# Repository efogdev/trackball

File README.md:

## Endgame Trackball (hardware)

#### Why 6 layers?

Because it's cheaper than 4 layers. Yes, seriously.

#### Stackup

JLC06161H-3313

#### Also see

Parent repo: https://github.com/efogtech/endgame-trackball

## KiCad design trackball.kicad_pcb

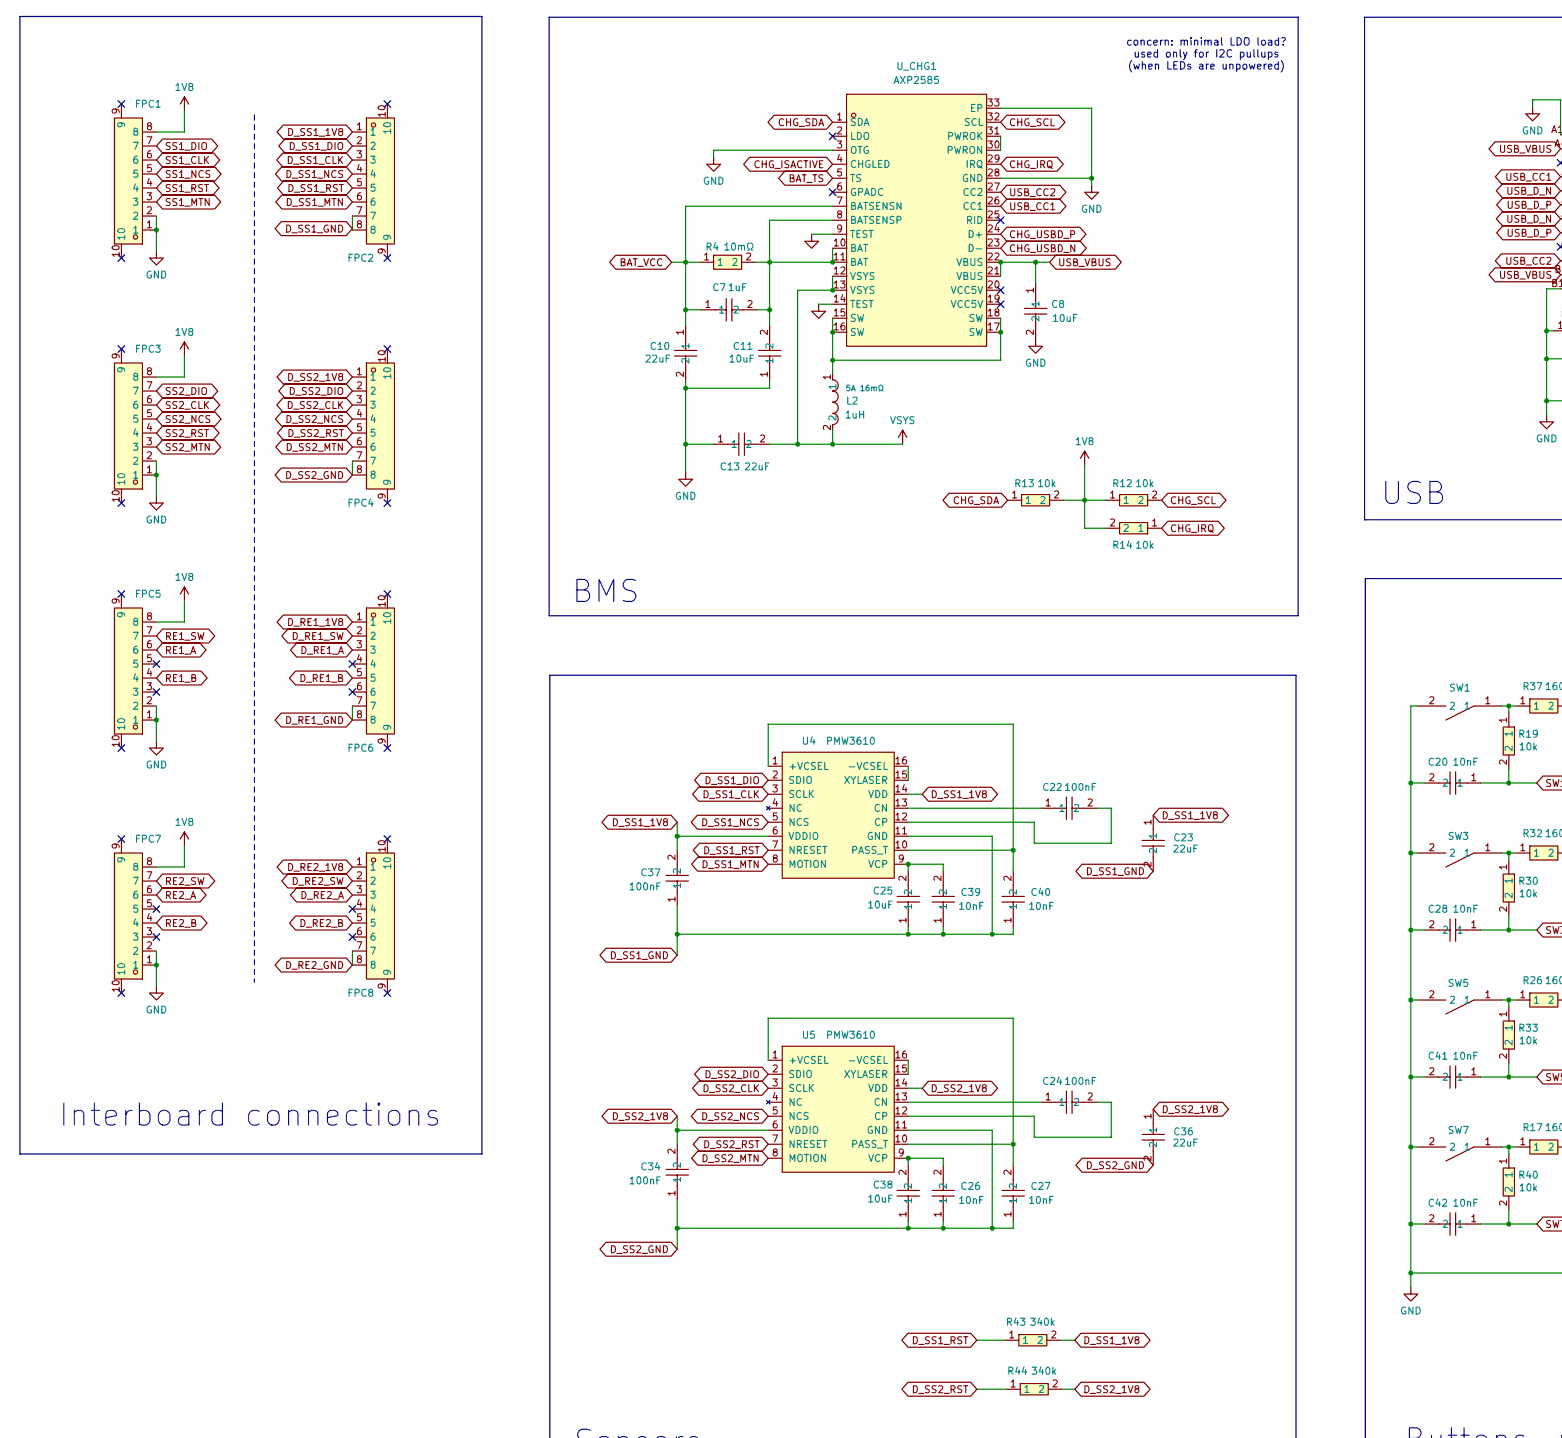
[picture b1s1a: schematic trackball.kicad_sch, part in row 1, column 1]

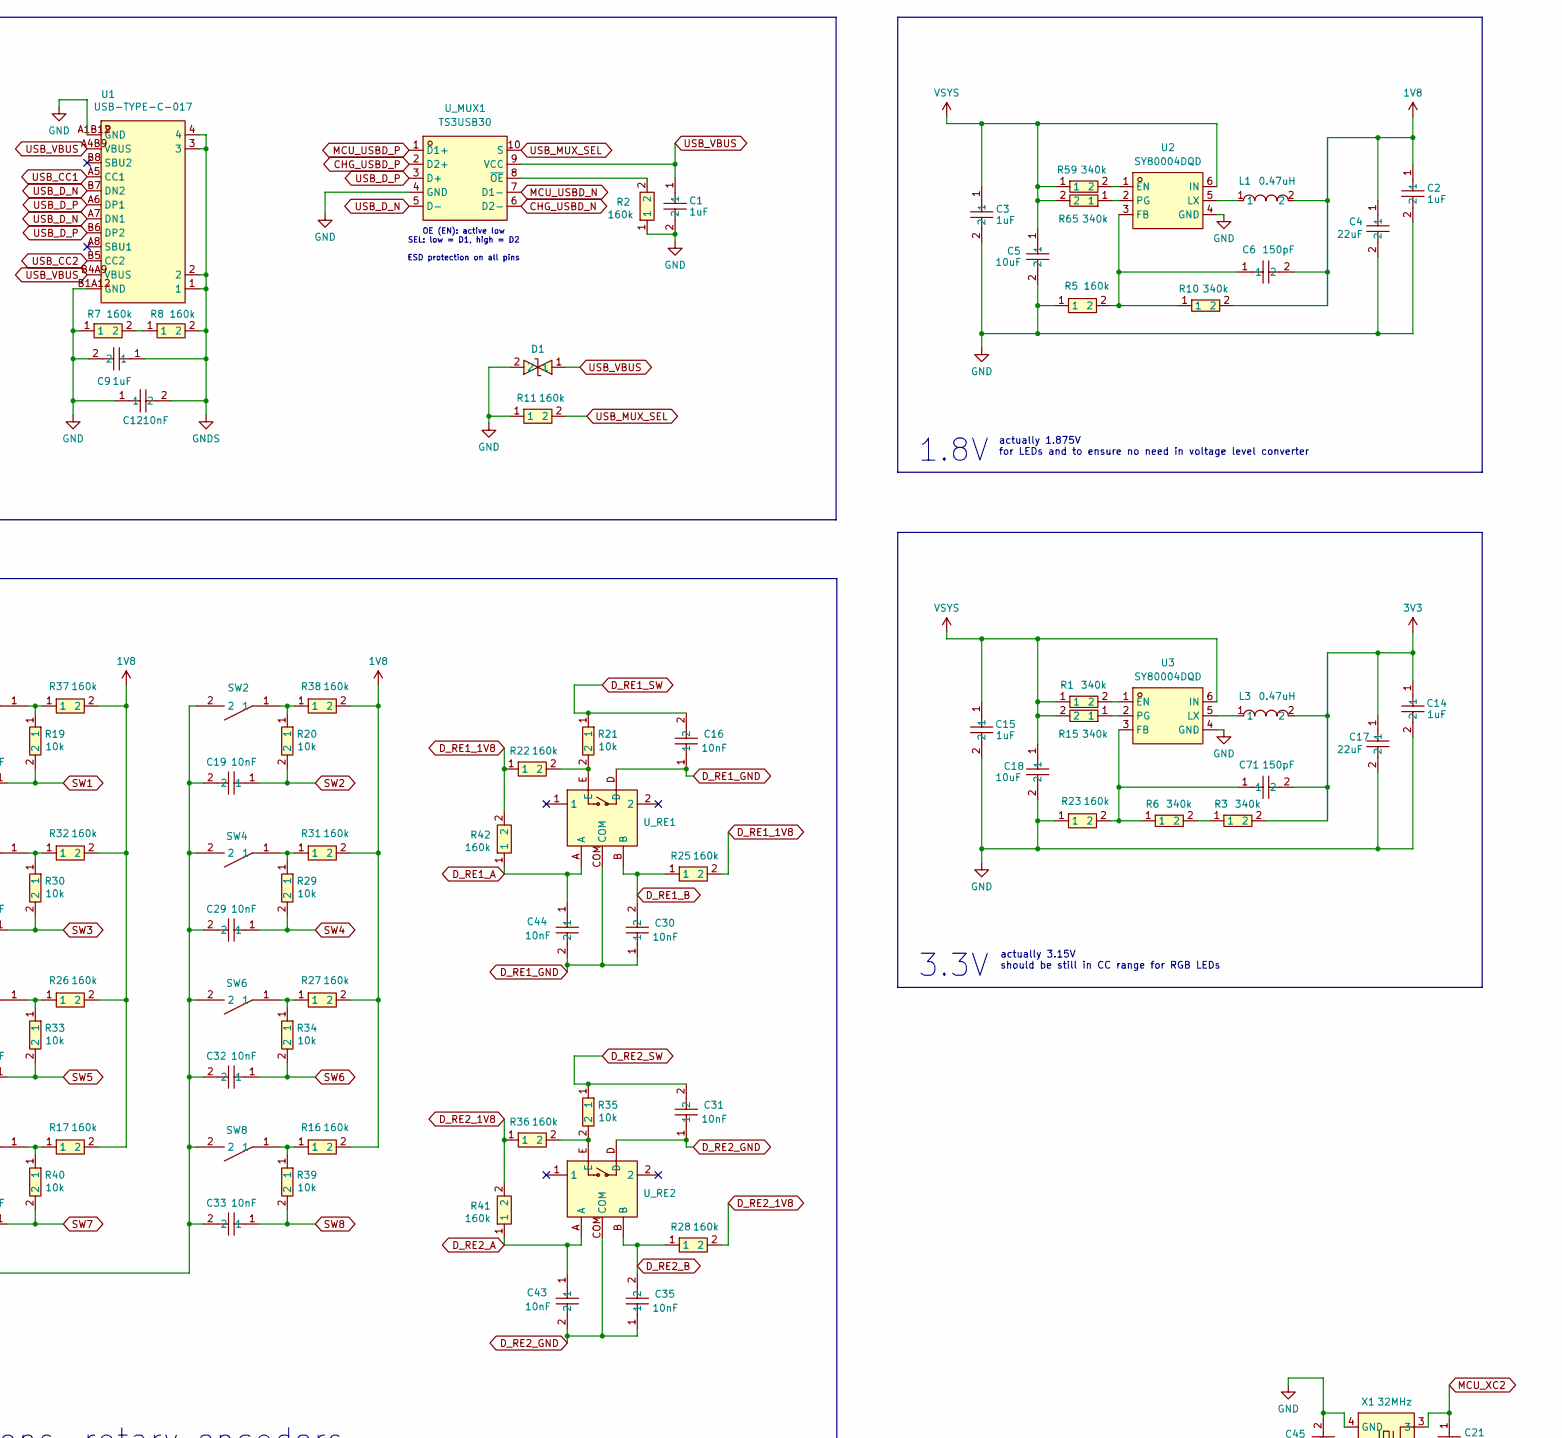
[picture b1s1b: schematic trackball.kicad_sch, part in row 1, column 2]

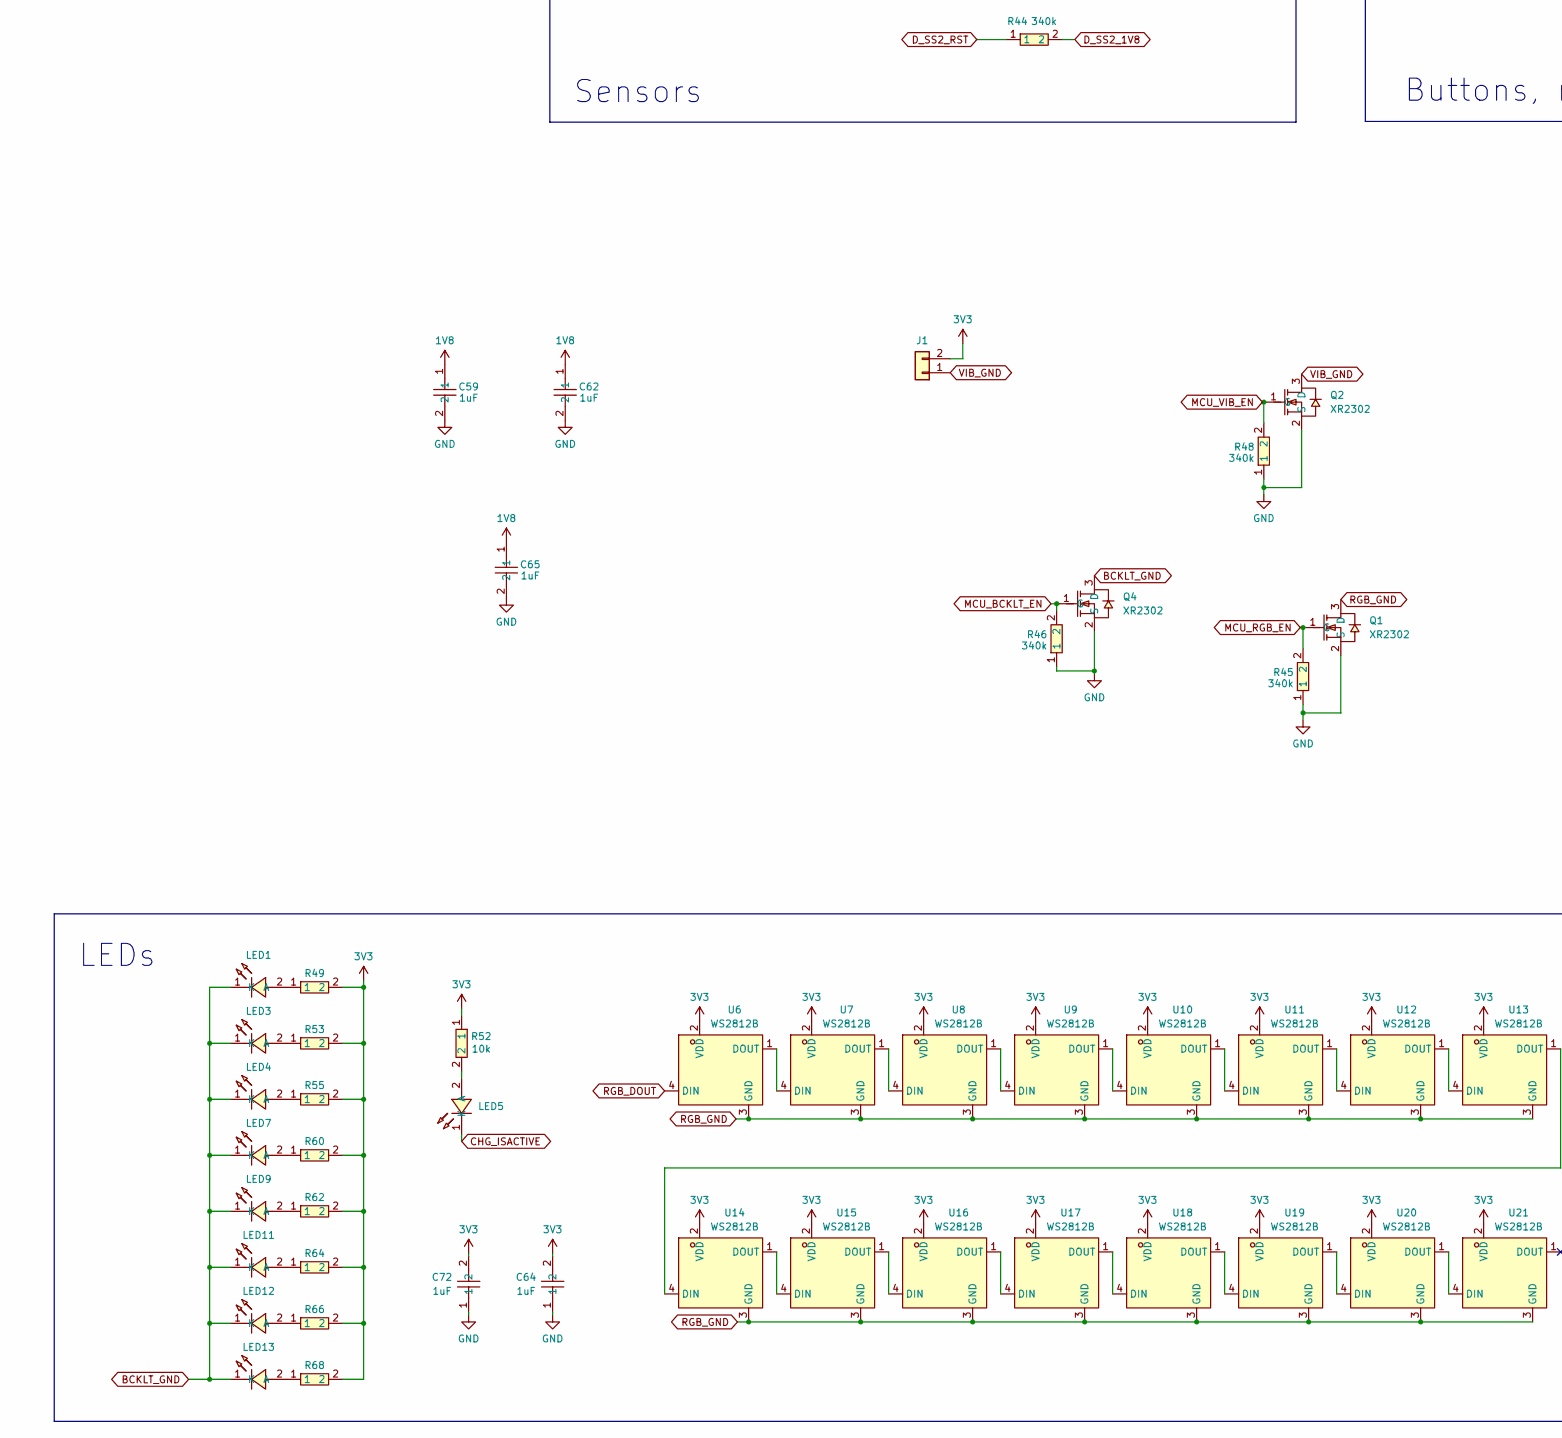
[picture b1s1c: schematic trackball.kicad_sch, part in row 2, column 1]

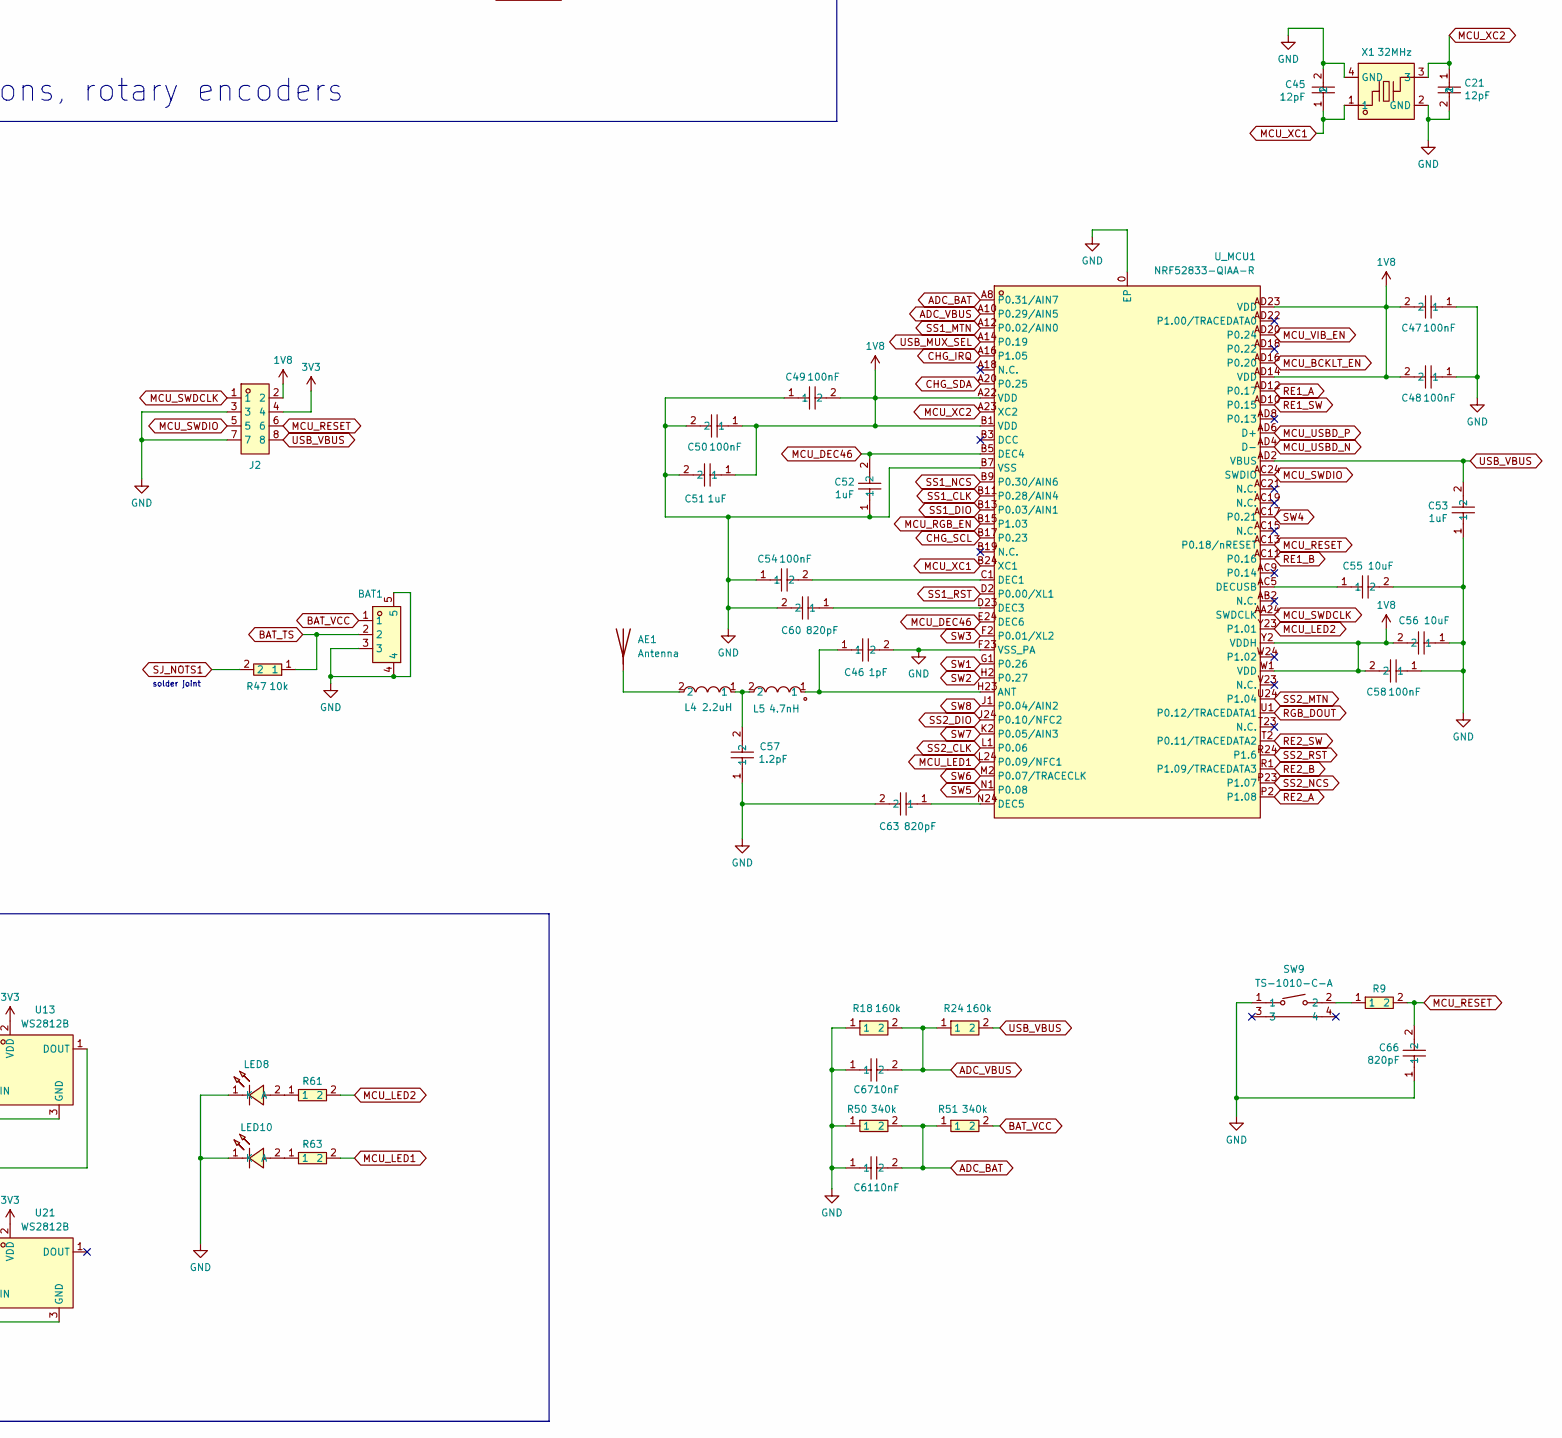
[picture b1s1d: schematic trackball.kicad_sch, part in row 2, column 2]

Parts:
AE1: Antenna; Texas_SWRA117D_2.4GHz_Left
BAT1: HCZZ0032-3; CONN-SMD_HCZZ0032-3; LCSC Part C7433424
C1, C2, C3, C7, C9, C14, C15, C51, C52, C53, C59, C62, C64, C65, C72: CGA0201X5R105M6R3ET; C0201; LCSC Part C6119749
C4, C10, C13, C17, C23, C36: GRM155R60J226ME11D; C0402; LCSC Part C415703
C5, C8, C11, C18, C25, C38, C55, C56: CL05A106MP5NUNC_C315248; C0402; LCSC Part C315248
C6, C71: C0201; LCSC Part C18213206
C12, C16, C19, C20, C26, C27, C28, C29, C30, C31, C32, C33, C35, C39, C40, C41, C42, C43, C44, C61, C67: 0201B103K160NT; C0201; LCSC Part C285154
C21, C45: 0201CG120J500NT; C0201; LCSC Part C50391
C22, C24, C34, C37, C47, C48, C49, C50, C54, C58: CGA0201X5R104K100ET; C0201; LCSC Part C6119757
C46: 0201CG1R0C250NT; C0201; LCSC Part C301901
C57: CGA0201C0G1R2C500ET; C0201; LCSC Part C22374839
C60, C63, C66: 0201B821K500NT; C0201; LCSC Part C2836759
D1: 0402ESDA-05N; D0402-BI; LCSC Part C316049
FPC1, FPC2, FPC3, FPC4, FPC5, FPC6, FPC7, FPC8: AFH34-S08FIA-1H; FPC-SMD_8P-P0.50_JS_AFH34-S08FIA-1H; LCSC Part C5139822
J1: Conn_01x02
J2: ZX-PM2.0-2-4PY; HDR-TH_8P-P2.00-V-F-R2-C4-S2.00; LCSC Part C7499368
L1, L3: FTC252012SR47MBCA; IND-SMD_L2.5-W2.0; LCSC Part C5832368
L2: FTC252012S1R0MBCD; L1008; LCSC Part C22400405
L4: LQG15HS2N2S02D; L0402; LCSC Part C86061
L5: LQG15HS4N7S02D; L0402-R-RD; LCSC Part C86065
LED1, LED3, LED4, LED7, LED9, LED11, LED12, LED13: SZYY0402W; LED0402-RD_WHITE; LCSC Part C434448
LED5: XL-1005UGC; LED0402-RD_GREEN; LCSC Part C965793
LED8, LED10: TZ-P2-0402RTIA1-0.45T; LED0402-RD_RED; LCSC Part C779449
Q1, Q2, Q4: XR2302; SOT-23-3_L2.9-W1.3-P0.95-LS2.4-BR; LCSC Part C42456447
R1, R3, R6, R10, R12, R13, R14, R15, R19, R20, R21, R29, R30, R33, R34, R35, R39, R40, R43, R44, R45, R46, R47, R48, R50, R51, R52, R59, R65: RC-01W103JT; R0201; LCSC Part C304504
R2, R5, R7, R8, R11, R16, R17, R18, R22, R23, R24, R25, R26, R27, R28, R31, R32, R36, R37, R38, R41, R42: 0201WMF1603TEE; R0201; LCSC Part C423714
R4: FRM121WFR010TM; R1206; LCSC Part C7467248
R9, R49, R53, R55, R60, R61, R62, R63, R64, R66, R68: RT0402BRE0750RL; R0402; LCSC Part C853312
SW1, SW2, SW3, SW4, SW5, SW6, SW7, SW8: HX TC-5608-Y; SW-SMD_TC-5608-Y; LCSC Part C25168853
SW9: TS-1010-C-A; KEY-SMD_TX-1010-X-X; LCSC Part C692458
U1: USB-TYPE-C-017; USB-TYPE-C-SMD_C9900008089; LCSC Part C2927037
U2, U3: SY80004DQD; VSON-6_L1.5-W1.5-P0.50-TL; LCSC Part C20617244
U4, U5: PMW3610
U6, U7, U8, U9, U10, U11, U12, U13, U14, U15, U16, U17, U18, U19, U20, U21: WS2812B; LED-SMD_4P-L1.0-W1.0-TL_XL-1010RGBC-WS2812B; LCSC Part C5349953
U_CHG1: AXP2585; QFN-32_L5.0-W5.0-P0.40-TL-EP2.9; LCSC Part C20199912
U_MCU1: NRF52833-QIAA-R; AQFN-73_L7.0-W7.0-P0.50-BL-EP4.8; LCSC Part C504799
U_MUX1: TS3USB30; UQFN-10_L1.8-W1.4-P0.40-TL; LCSC Part C73880
U_RE1, U_RE2: GT-EVA01AA-L1; RES-ADJ-SMD_GT-EVA01AA-L1; LCSC Part C17702124
X1: XL7EL89CKI-111YLC-32M; CRYSTAL-SMD_4P-L2.0-W1.6-BL; LCSC Part C2965582

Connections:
1V8: C2.1, C4.1, C6.2, C47.2, C48.2, C49.2, C50.1, C51.1, C56.2, C58.2, C59.1, C62.1, C65.1, FPC1.8, FPC3.8, FPC5.8, FPC7.8, J2.2, L1.2, R10.2, R12.1, R13.2, R14.2, R16.2, R17.2, R26.2, R27.2, R31.2, R32.2, R37.2, R38.2, U_MCU1.A22 (VDD), U_MCU1.AD14 (VDD), U_MCU1.AD23 (VDD), U_MCU1.B1 (VDD), U_MCU1.W1 (VDD), U_MCU1.Y2 (VDDH)
3V3: C14.1, C17.1, C64.2, C71.2, C72.2, J1.2, J2.4, L3.2, R3.2, R49.2, R52.1, R53.2, R55.2, R60.2, R62.2, R64.2, R66.2, R68.2, U6.2 (VDD), U7.2 (VDD), U8.2 (VDD), U9.2 (VDD), U10.2 (VDD), U11.2 (VDD), U12.2 (VDD), U13.2 (VDD), U14.2 (VDD), U15.2 (VDD), U16.2 (VDD), U17.2 (VDD), U18.2 (VDD), U19.2 (VDD), U20.2 (VDD), U21.2 (VDD)
ADC_BAT: C61.2, R50.2, R51.1, U_MCU1.A8 (P0.31/AIN7)
ADC_VBUS: C67.2, R18.2, R24.1, U_MCU1.A10 (P0.29/AIN5)
BAT_TS: BAT1.2, R47.1, U_CHG1.5 (TS)
BAT_VCC: BAT1.1, C7.1, C10.1, R4.1, R51.2, U_CHG1.7 (BATSENSN)
BCKLT_GND: LED1.1 (K), LED3.1 (K), LED4.1 (K), LED7.1 (K), LED9.1 (K), LED11.1 (K), LED12.1 (K), LED13.1 (K), Q4.3 (D)
CHG_IRQ: R14.1, U_CHG1.29 (IRQ), U_MCU1.A16 (P1.05)
CHG_ISACTIVE: LED5.1 (K), U_CHG1.4 (CHGLED)
CHG_SCL: R12.2, U_CHG1.32 (SCL), U_MCU1.B17 (P0.23)
CHG_SDA: R13.1, U_CHG1.1 (SDA), U_MCU1.A20 (P0.25)
CHG_USBD_N: U_CHG1.23 (D-), U_MUX1.6 (D2-)
CHG_USBD_P: U_CHG1.24 (D+), U_MUX1.2 (D2+)
D_RE1_1V8: FPC6.1, R22.1, R25.2, R42.2
D_RE1_A: C44.1, FPC6.3, R42.1, U_RE1.A
D_RE1_B: C30.2, FPC6.5, R25.1, U_RE1.B
D_RE1_GND: C16.1, C30.1, C44.2, FPC6.7, FPC6.8, U_RE1.COM, U_RE1.D
D_RE1_SW: C16.2, FPC6.2, R21.1
D_RE2_1V8: FPC8.1, R28.2, R36.1, R41.2
D_RE2_A: C43.1, FPC8.3, R41.1, U_RE2.A
D_RE2_B: C35.2, FPC8.5, R28.1, U_RE2.B
D_RE2_GND: C31.1, C35.1, C43.2, FPC8.7, FPC8.8, U_RE2.COM, U_RE2.D
D_RE2_SW: C31.2, FPC8.2, R35.1
D_SS1_1V8: C23.1, C37.2, FPC2.1, R43.2, U4.6 (VDDIO), U4.14 (VDD)
D_SS1_CLK: FPC2.3, U4.3 (SCLK)
D_SS1_DIO: FPC2.2, U4.2 (SDIO)
D_SS1_GND: C23.2, C25.1, C37.1, C39.1, C40.1, FPC2.7, FPC2.8, U4.11 (GND)
D_SS1_MTN: FPC2.6, U4.8 (MOTION)
D_SS1_NCS: FPC2.4, U4.5 (NCS)
D_SS1_RST: FPC2.5, R43.1, U4.7 (NRESET)
D_SS2_1V8: C34.2, C36.1, FPC4.1, R44.2, U5.6 (VDDIO), U5.14 (VDD)
D_SS2_CLK: FPC4.3, U5.3 (SCLK)
D_SS2_DIO: FPC4.2, U5.2 (SDIO)
D_SS2_GND: C26.1, C27.1, C34.1, C36.2, C38.1, FPC4.7, FPC4.8, U5.11 (GND)
D_SS2_MTN: FPC4.6, U5.8 (MOTION)
D_SS2_NCS: FPC4.4, U5.5 (NCS)
D_SS2_RST: FPC4.5, R44.1, U5.7 (NRESET)
GNDS: C9.1, C12.2, R8.2, U1.1, U1.2, U1.3, U1.4
MCU_BCKLT_EN: Q4.1 (G), R46.2, U_MCU1.AD16 (P0.20)
MCU_DEC46: C52.2, U_MCU1.B5 (DEC4), U_MCU1.E24 (DEC6)
MCU_LED1: R63.2, U_MCU1.L24 (P0.09/NFC1)
MCU_LED2: R61.2, U_MCU1.Y23 (P1.01)
MCU_RESET: C66.2, J2.6, R9.2, U_MCU1.AC13 (P0.18/nRESET)
MCU_RGB_EN: Q1.1 (G), R45.2, U_MCU1.B15 (P1.03)
MCU_SWDCLK: J2.1, U_MCU1.AA24 (SWDCLK)
MCU_SWDIO: J2.5, U_MCU1.AC24 (SWDIO)
MCU_USBD_N: U_MCU1.AD4 (D-), U_MUX1.7 (D1-)
MCU_USBD_P: U_MCU1.AD6 (D+), U_MUX1.1 (D1+)
MCU_VIB_EN: Q2.1 (G), R48.2, U_MCU1.AD20 (P0.24)
MCU_XC1: C45.1, U_MCU1.B24 (XC1), X1.1
MCU_XC2: C21.1, U_MCU1.A23 (XC2), X1.3
unnamed: AE1.1 (A), L4.2
unnamed: C57.2, L4.1, L5.2
unnamed: L2.1, U_CHG1.15 (SW), U_CHG1.16 (SW), U_CHG1.17 (SW), U_CHG1.18 (SW)
unnamed: LED1.2 (A), R49.1
unnamed: LED3.2 (A), R53.1
unnamed: LED4.2 (A), R55.1
unnamed: LED5.2 (A), R52.2
unnamed: LED7.2 (A), R60.1
unnamed: LED8.2 (A), R61.1
unnamed: LED9.2 (A), R62.1
unnamed: LED10.2 (A), R63.1
unnamed: LED11.2 (A), R64.1
unnamed: LED12.2 (A), R66.1
unnamed: LED13.2 (A), R68.1
unnamed: R3.1, R6.2
unnamed: R7.2, R8.1
unnamed: R9.1, SW9.2
unnamed: R16.1, R39.1, SW8.1
unnamed: R17.1, R40.1, SW7.1
unnamed: R19.1, R37.1, SW1.1
unnamed: R20.1, R38.1, SW2.1
unnamed: R21.2, R22.2, U_RE1.E
unnamed: R26.1, R33.1, SW5.1
unnamed: R27.1, R34.1, SW6.1
unnamed: R29.1, R31.1, SW4.1
unnamed: R30.1, R32.1, SW3.1
unnamed: R35.2, R36.2, U_RE2.E
unnamed: R59.2, U2.1 (EN)
unnamed: C6.1, R5.2, R10.1, U2.3 (FB)
unnamed: L1.1, U2.5 (LX)
unnamed: R65.1, U2.2 (PG)
unnamed: R1.2, U3.1 (EN)
unnamed: C71.1, R6.1, R23.2, U3.3 (FB)
unnamed: L3.1, U3.5 (LX)
unnamed: R15.1, U3.2 (PG)
unnamed: C40.2, U4.1 (+VCSEL), U4.10 (PASS_T)
unnamed: U4.15 (XYLASER), U4.16 (-VCSEL)
unnamed: C22.1, U4.13 (CN)
unnamed: C22.2, U4.12 (CP)
unnamed: C25.2, C39.2, U4.9 (VCP)
unnamed: C27.2, U5.1 (+VCSEL), U5.10 (PASS_T)
unnamed: U5.15 (XYLASER), U5.16 (-VCSEL)
unnamed: C24.1, U5.13 (CN)
unnamed: C24.2, U5.12 (CP)
unnamed: C26.2, C38.2, U5.9 (VCP)
unnamed: U6.1 (DOUT), U7.4 (DIN)
unnamed: U7.1 (DOUT), U8.4 (DIN)
unnamed: U8.1 (DOUT), U9.4 (DIN)
unnamed: U9.1 (DOUT), U10.4 (DIN)
unnamed: U10.1 (DOUT), U11.4 (DIN)
unnamed: U11.1 (DOUT), U12.4 (DIN)
unnamed: U12.1 (DOUT), U13.4 (DIN)
unnamed: U13.1 (DOUT), U14.4 (DIN)
unnamed: U14.1 (DOUT), U15.4 (DIN)
unnamed: U15.1 (DOUT), U16.4 (DIN)
unnamed: U16.1 (DOUT), U17.4 (DIN)
unnamed: U17.1 (DOUT), U18.4 (DIN)
unnamed: U18.1 (DOUT), U19.4 (DIN)
unnamed: U19.1 (DOUT), U20.4 (DIN)
unnamed: U20.1 (DOUT), U21.4 (DIN)
unnamed: C7.2, C11.2, R4.2, U_CHG1.8 (BATSENSP), U_CHG1.10 (BAT), U_CHG1.11 (BAT)
unnamed: U_CHG1.30 (PWRON), U_CHG1.31 (PWROK)
unnamed: C46.1, L5.1, U_MCU1.H23 (ANT)
unnamed: C54.2, U_MCU1.C1 (DEC1)
unnamed: C60.1, U_MCU1.D23 (DEC3)
unnamed: C63.1, U_MCU1.N24 (DEC5)
unnamed: C55.1, U_MCU1.AC5 (DECUSB)
unnamed: R2.2, U_MUX1.8 (~OE)
RE1_A: FPC5.6, U_MCU1.AD12 (P0.17)
RE1_B: FPC5.4, U_MCU1.AC11 (P0.16)
RE1_SW: FPC5.7, U_MCU1.AD10 (P0.15)
RE2_A: FPC7.6, U_MCU1.P2 (P1.08)
RE2_B: FPC7.4, U_MCU1.R1 (P1.09/TRACEDATA3)
RE2_SW: FPC7.7, U_MCU1.T2 (P0.11/TRACEDATA2)
RGB_DOUT: U6.4 (DIN), U_MCU1.U1 (P0.12/TRACEDATA1)
RGB_GND: Q1.3 (D), U6.3 (GND), U7.3 (GND), U8.3 (GND), U9.3 (GND), U10.3 (GND), U11.3 (GND), U12.3 (GND), U13.3 (GND), U14.3 (GND), U15.3 (GND), U16.3 (GND), U17.3 (GND), U18.3 (GND), U19.3 (GND), U20.3 (GND), U21.3 (GND)
SJ_NOTS1: R47.2
SS1_CLK: FPC1.6, U_MCU1.B11 (P0.28/AIN4)
SS1_DIO: FPC1.7, U_MCU1.B13 (P0.03/AIN1)
SS1_MTN: FPC1.3, U_MCU1.A12 (P0.02/AIN0)
SS1_NCS: FPC1.5, U_MCU1.B9 (P0.30/AIN6)
SS1_RST: FPC1.4, U_MCU1.D2 (P0.00/XL1)
SS2_CLK: FPC3.6, U_MCU1.L1 (P0.06)
SS2_DIO: FPC3.7, U_MCU1.J24 (P0.10/NFC2)
SS2_MTN: FPC3.3, U_MCU1.U24 (P1.04)
SS2_NCS: FPC3.5, U_MCU1.P23 (P1.07)
SS2_RST: FPC3.4, U_MCU1.R24 (P1.6)
SW1: C20.1, R19.2, U_MCU1.G1 (P0.26)
SW2: C19.1, R20.2, U_MCU1.H2 (P0.27)
SW3: C28.1, R30.2, U_MCU1.F2 (P0.01/XL2)
SW4: C29.1, R29.2, U_MCU1.AC17 (P0.21)
SW5: C41.1, R33.2, U_MCU1.N1 (P0.08)
SW6: C32.1, R34.2, U_MCU1.M2 (P0.07/TRACECLK)
SW7: C42.1, R40.2, U_MCU1.K2 (P0.05/AIN3)
SW8: C33.1, R39.2, U_MCU1.J1 (P0.04/AIN2)
USB_CC1: U1.A5 (CC1), U_CHG1.26 (CC1)
USB_CC2: U1.B5 (CC2), U_CHG1.27 (CC2)
USB_D_N: U1.A7 (DN1), U1.B7 (DN2), U_MUX1.5 (D-)
USB_D_P: U1.A6 (DP1), U1.B6 (DP2), U_MUX1.3 (D+)
USB_MUX_SEL: R11.2, U_MCU1.A14 (P0.19), U_MUX1.10 (S)
USB_VBUS: C1.1, C8.1, C53.2, D1.1, J2.8, R24.2, U1.A4B9 (VBUS), U1.B4A9 (VBUS), U_CHG1.21 (VBUS), U_CHG1.22 (VBUS), U_MCU1.AD2 (VBUS), U_MUX1.9 (VCC)
VIB_GND: J1.1, Q2.3 (D)
VSYS: C3.1, C5.1, C13.2, C15.1, C18.1, L2.2, R1.1, R15.2, R59.1, R65.2, U2.6 (IN), U3.6 (IN), U_CHG1.12 (VSYS), U_CHG1.13 (VSYS)

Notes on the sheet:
LEDs
Interboard connections
Buttons, rotary encoders
BMS
USB
actually 3.15V should be still in CC range for RGB LEDs
actually 1.875V for LEDs and to ensure no need in voltage level converter
3.3V
Sensors
concern: minimal LDO load? used only for I2C pullups (when LEDs are unpowered)
solder joint
1.8V
OE (EN): active low SEL: low = D1, high = D2 ESD protection on all pins

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
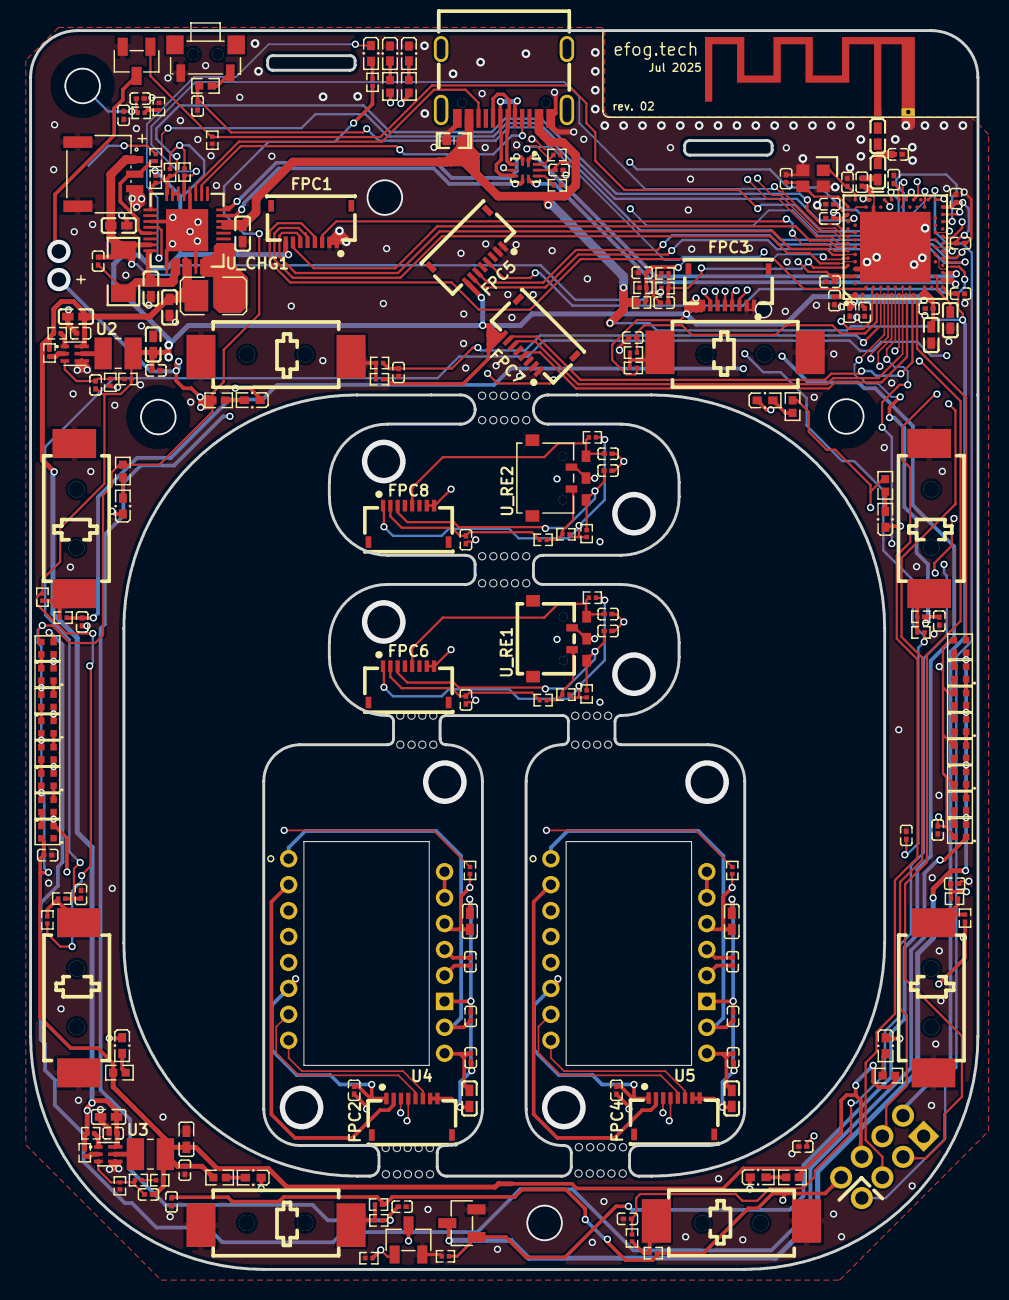
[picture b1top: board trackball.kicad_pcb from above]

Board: 4 copper layers, 65.0 x 85.0 mm, 199 parts (0 on the bottom side), 154 nets.

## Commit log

2025-05-24 feat: license
2025-05-24 chore: checkpoint
2025-05-26 chore: readme
2025-07-12 feat: rev.02 hardware
2025-07-12 bugfix: mount holes soldermask
2025-07-12 chore: refactoring
2025-08-05 feat: rev.03 hardware
2025-08-06 feat: wakeup source
2025-08-06 chore: image
2025-08-07 bugfix: wakeup source 3V3 → 1V8 pullup
2025-08-18 bugfix: pmw3610 sensor clearance
